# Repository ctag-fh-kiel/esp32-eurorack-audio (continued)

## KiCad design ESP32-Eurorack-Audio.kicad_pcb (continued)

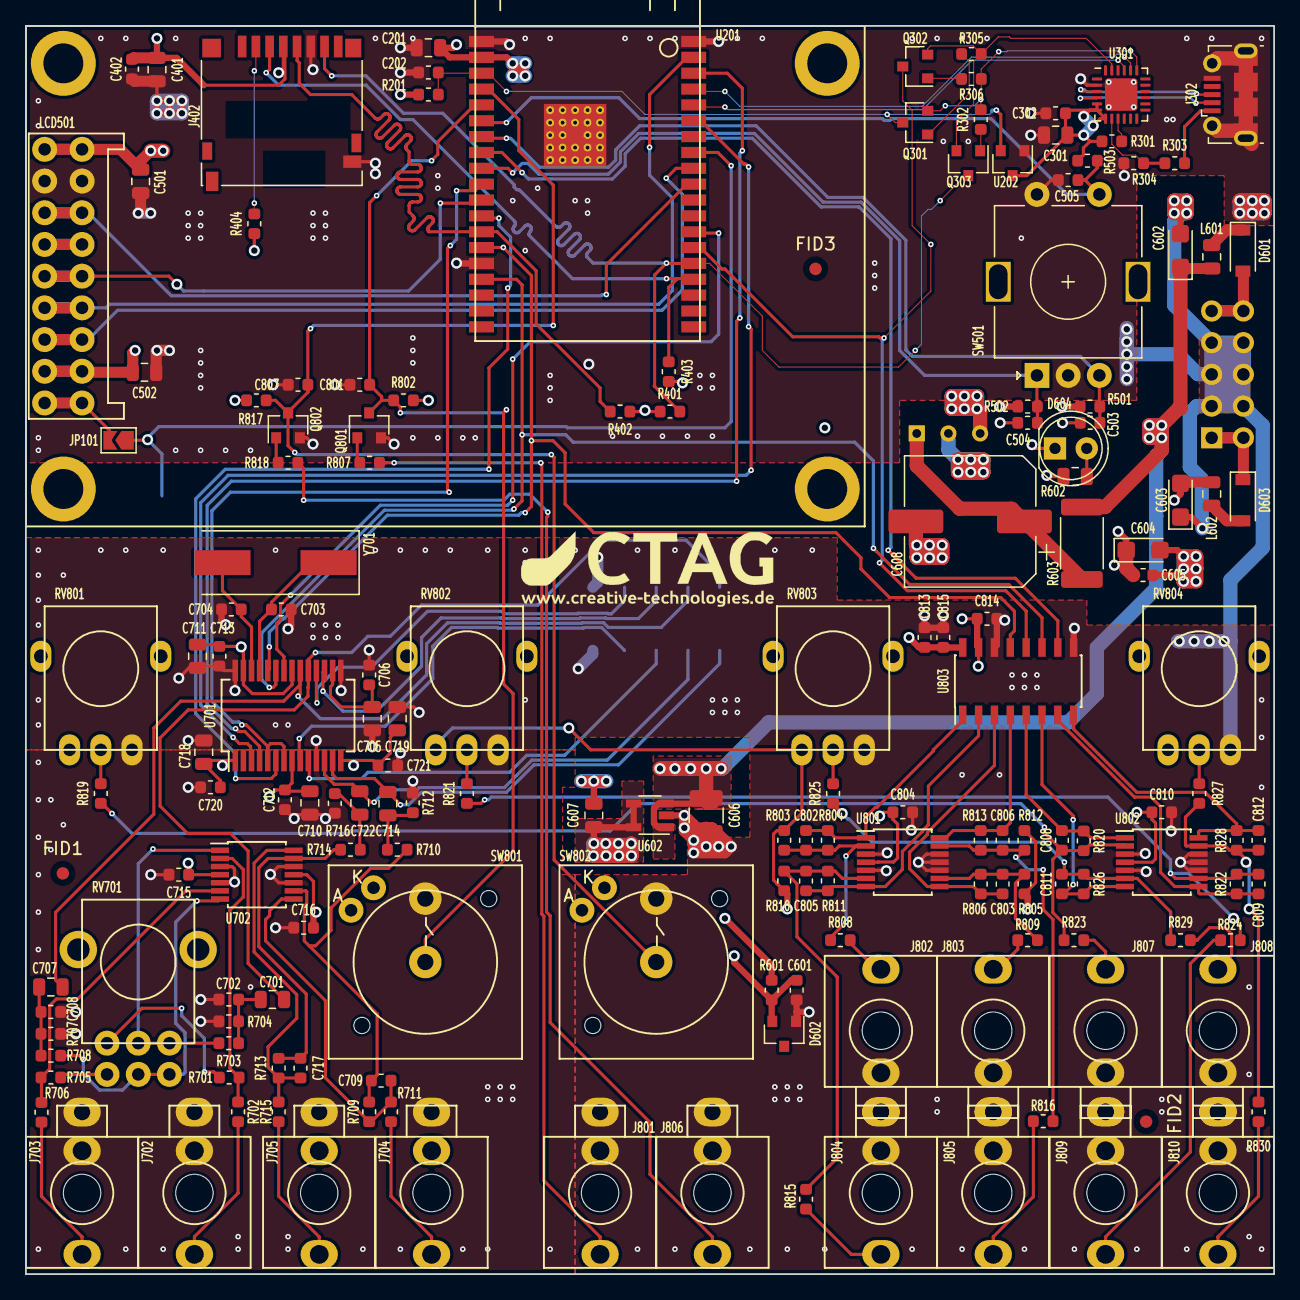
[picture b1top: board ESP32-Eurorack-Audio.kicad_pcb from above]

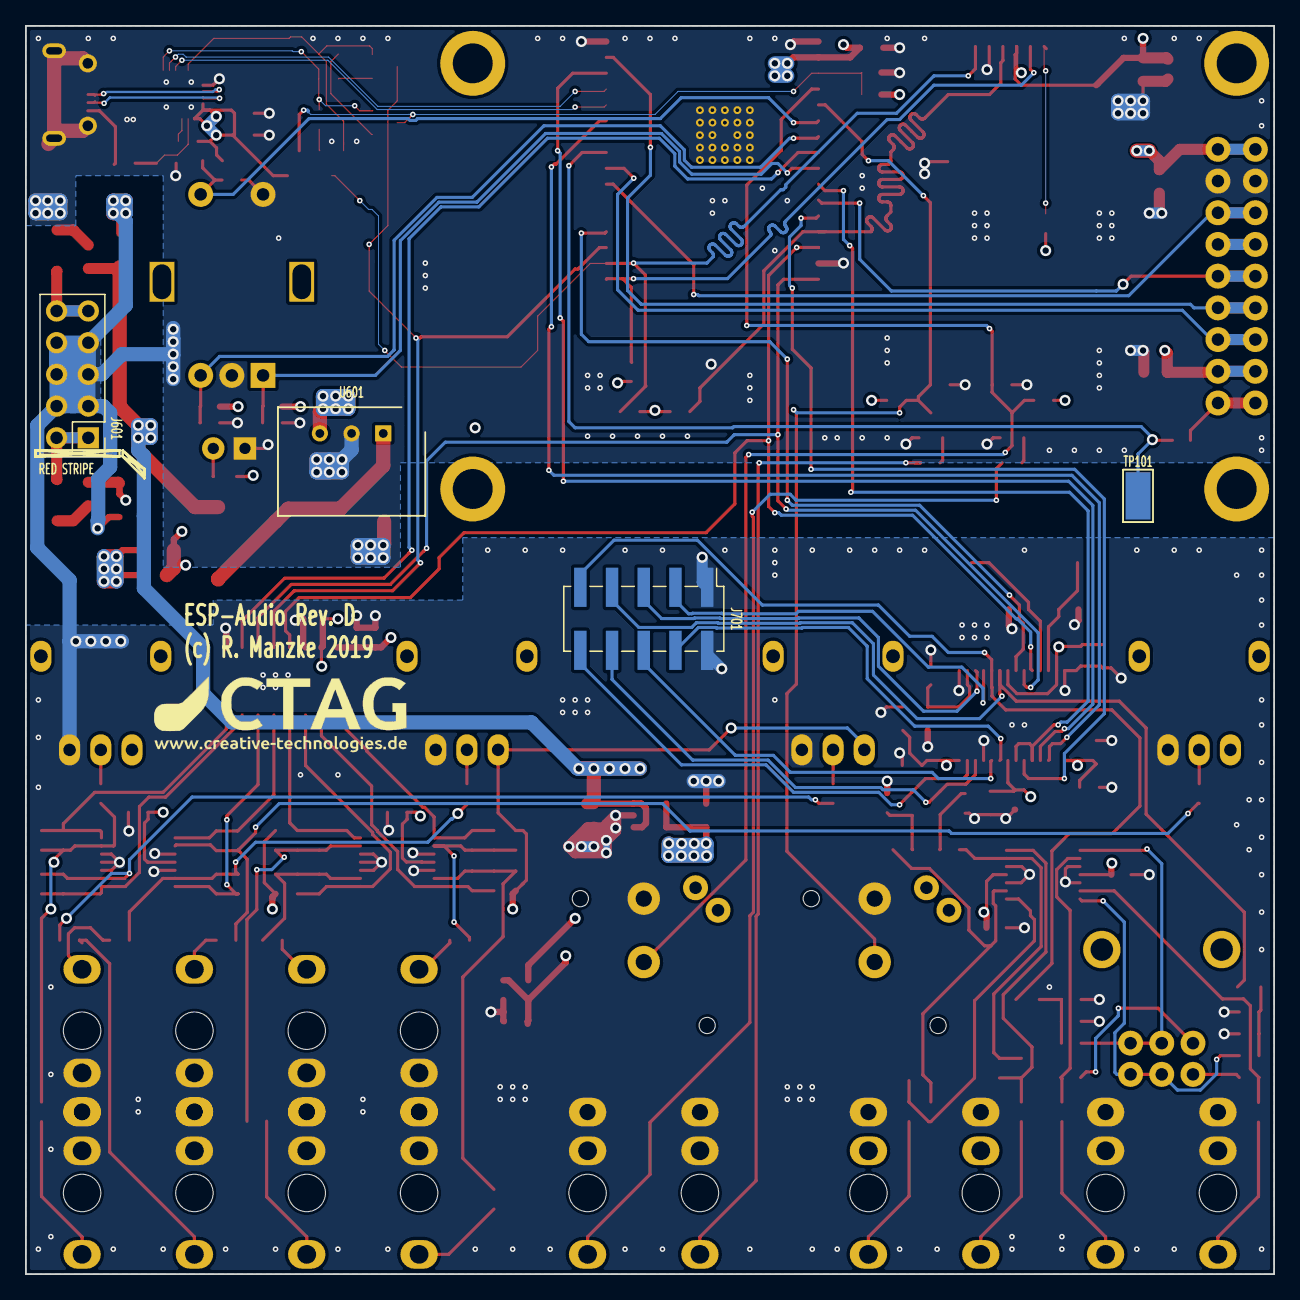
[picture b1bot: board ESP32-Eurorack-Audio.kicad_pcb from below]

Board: 4 copper layers, 100.0 x 100.0 mm, 171 parts (4 on the bottom side), 110 nets.

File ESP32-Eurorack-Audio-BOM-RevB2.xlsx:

Id | Designator | Package | Quantity | Designation | Mouser | Remarks
1 | C813,C302,C402,C601,C605,C706,C712,C715,C716,C720,C721,C801,C804,C807,C810,C713 | C_0603_1608Metric | 16 | 100n | 81-GRM033C71C104KE4J
2 | C815,C814 | C_0603_1608Metric | 2 | 1u | 710-885012206034
3 | U201 | ESP32-WROVER | 1 | ESP32-WROVER | 356-ESP32-WROB(16MB)
 | LCD501 | Connector | 1 |  | MDF7-9S-2.54DSA(55) and MDF7-5S-2.54DSA(55)
4 | LCD501 | TFT_2.2 | 1 | TFT_ILI9341 | https://www.aliexpress.com/item/Smart-Electronics-2-2-Inch-2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 | 2.2" TFT ILI9341 e.g. Aliexpress
5 | C201,C401,C501,C607,C701,C705,C707,C710,C714,C718,C719,C722,C502,C301,C711 | C_0805_2012Metric | 15 | 10u | 81-GRM21BR70J106KA3L
6 | C202 | C_0603_1608Metric | 1 | 3.3u | 963-EMK316B7335KL-T
7 | C204,C802,C803,C805,C806,C808,C809,C811,C812 | C_0603_1608Metric | 9 | 1n | 77-VJ0603Y102KXQCBC
8 | C602,C603,C604 | CP_EIA-3216-12_Kemet-S | 3 | 22u | 581-F951C226KQAAQ2
9 | C702,C708 | C_0603_1608Metric | 2 | 220p | 710-885012206055
10 | C703,C704,C709,C717 | C_0603_1608Metric | 4 | 18p | 80-C0603C180J5G
11 | D301,D601,D603 | D_SOD-123 | 3 | STPS2L40ZFY | 511-STPS2L40ZFY
12 | D302,D401,D402 | SOT-143 | 3 | SP0503BAHT | 576-SP0503BAHTG
13 | D602 | SOT-23 | 1 | LM4040B-10 | 595-LM4040B10IDBZR
14 | D604 | LED_1206_3216Metric_Castellated | 1 | APTD3216SURCK | 604-APTD-3216SURCK
15 | J302 | USB_Micro-B_Molex-105017-0001 | 1 | USB_B_Micro | 105017-0001
16 | J402 | microSD_HC_Hirose_DM3D-SF | 1 | Micro_SD_Card | 798-DM3D-SF
17 | J601 | PinHeader_2x05_P2.54mm_Vertical | 1 | PWR |  | Standard pin header
28 | JP601 | PinHeader_1x03_P2.54mm_Vertical | 1 | VSEL |  | Standard pin header
29 | L301,L601,L602 | C_0805_2012Metric | 3 | 600 | 623-2508056017Y2
30 | Q301,Q302,Q303,Q801,Q802 | SOT-23 | 5 | SS8050-G | 750-SS8050-G
34 | SW201 | SW_SPST_PTS810 | 1 | EN | 611-PTS810SJK250SMTR | Only for test config, not required in production
35 | SW203 | SW_SPST_PTS810 | 1 | FLASH | 611-PTS810SJK250SMTR | Only for test config, not required in production
36 | SW501 | RotaryEncoder_Alps_EC11E-Switch_Vertical_H20mm | 1 | SEL | https://www.aliexpress.com/item/10pcs-Rotary-encoder-code-sw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 | eg Aliexpress
37 | SW801 | SW_6425 | 2 | TRG0 | 979-826.000.071
38 | SW802 | SW_6425 | 2 | TRG1 | 979-6425.0101
39 | U301 | QFN-24-1EP_4x4mm_P0.5mm_EP2.6x2.6mm | 1 | CP2102N-A01-GQFN24 | 634-CP2102NA01GQFN24
40 | U601 | TO-252-2 | 1 | LM1117-3.3 | 926-LM1117DT-3.3NOPB
41 | U602 | TSOT-23-5 | 1 | ADP7118 | 584-ADP7118AUJZ3.3R7
42 | U701 | SSOP-28_5.3x10.2mm_P0.65mm | 1 | WM8731 | 238-WM8731SEDS/V
43 | U702 | TSSOP-14_4.4x5mm_P0.65mm | 1 | TL074 | 595-TL074CPWR
44 | U801,U802 | TSSOP-14_4.4x5mm_P0.65mm | 2 | MCP6004 | 579-MCP6004-I/ST
45 | U803 | SOIC-16_3.9x9.9mm_P1.27mm | 1 | MCP3208 | 579-MCP3208T-CI/SL
46 | Y701 | Crystal_SMD_HC49-SD | 1 | 11.289600MHz | 815-ABLS211.2896B4YT
47 | R201,R301,R302,R305,R306,R401,R402,R403,R404,R501,R502,R503,R801,R802,R814,R817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 | R_0603_1608Metric | 17 | 10k | 652-CR0603FX-1002ELF
48 | R303 | R_0603_1608Metric | 1 | 22.1k | 652-CR0603FX-2212ELF
49 | R304 | R_0603_1608Metric | 1 | 47.5k | 603-RC0603FR-0747K5L
50 | R807,R808,R809,R815,R816,R818,R823,R824,R829,R830 | R_0603_1608Metric | 13 | 100k | 603-RC0603FR-07100KL
51 | R601 | R_0603_1608Metric | 1 | 220
52 | R602 | R_0805_2012Metric | 1 | 68 | 603-AC0603FR-0768RL
53 | R701,R705 | R_0603_1608Metric | 2 | 3k3 | 652-CR0603-FX3301ELF
54 | R702,R706 | R_0603_1608Metric | 2 | 22k | 652-CR0603FX-2202ELF
55 | R703,R704,R707,R708,R710,R714 | R_0603_1608Metric | 6 | 5k6 | 652-CR0603FX-5601ELF
56 | R709,R712,R713,R716 | R_0603_1608Metric | 4 | 39k | 652-CR0603FX-3902ELF
57 | R711,R715,R202,R204 | R_0603_1608Metric | 4 | 1k | 652-CR0603FX-1001ELF
58 | R803,R810 | R_0603_1608Metric | 2 | 180k | 652-CR0603FX-1803ELF
59 | R804,R811 | R_0603_1608Metric | 2 | 47k | 652-CR0603FX-4702ELF
60 | R805,R812,R819,R821,R825,R827 | R_0603_1608Metric | 6 | 200k | 652-CR0603FX-2003ELF
61 | R806,R813 | R_0603_1608Metric | 2 | 33k | 652-CR0603FX-3302ELF
62 | R820,R822,R826,R828 | R_0603_1608Metric | 4 | 66.5k | 652-CR0603-FX6652ELF
63 | J701 | PinHeader_2x05_P2.54mm_Vertical_SMD | 1 | AUEXT |  | Standard SMD pin header
64 | FID1,FID2,FID3 | Fiducial_1mm_Dia_2.54mm_Outer_CopperTop | 3 | ~ |  | Fiducials for pick and place
65 | C606 | C_1210_3225Metric | 1 | 10u | 963-EMK325B7106MN-T
66 | JP101,JP201,JP202 | SolderJumper-2_P1.3mm_Open_TrianglePad1.0x1.5mm | 3 | Jumper |  | Test configs
67 | Q201,Q202 | SOT-23 | 2 | BSS138 | 771-BSS138P215 | Only for test config, not required in production
68 | TP101 | TestPoint_Keystone_5019_Minature | 1 | TP_IO19 | 534-5019 | For testing purposes, only if needed
69 | TP301 | TestPoint_Keystone_5019_Minature | 1 | TP_EN | 534-5019 | For testing purposes, only if needed
70 | TP302 | TestPoint_Keystone_5019_Minature | 1 | TP_IO0 | 534-5019 | For testing purposes, only if needed
71 | TP303 | TestPoint_Keystone_5019_Minature | 1 | TP_IO2 | 534-5019 | For testing purposes, only if needed
72 | TP602 | TestPoint_Keystone_5019_Minature | 1 | TestPoint | 534-5019 | For testing purposes, only if needed
73 | TP801 | TestPoint_Keystone_5019_Minature | 1 | TA | 534-5019 | For testing purposes, only if needed
74 | TP802 | TestPoint_Keystone_5019_Minature | 1 | TB | 534-5019 | For testing purposes, only if needed
75 | TP803 | TestPoint_Keystone_5019_Minature | 1 | TC | 534-5019 | For testing purposes, only if needed
76 | TP304 | TestPoint_Keystone_5019_Minature | 1 | TP_RXD | 534-5019 | For testing purposes, only if needed
77 | TP305 | TestPoint_Keystone_5019_Minature | 1 | TP_TXD | 534-5019 | For testing purposes, only if needed
78 | TP306 | TestPoint_Keystone_5019_Minature | 1 | TP_DTR | 534-5019 | For testing purposes, only if needed
79 | TP307 | TestPoint_Keystone_5019_Minature | 1 | TP_RTS | 534-5019 | For testing purposes, only if needed

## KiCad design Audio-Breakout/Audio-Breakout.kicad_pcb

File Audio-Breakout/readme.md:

# Stereo line IO + headphones breakout board for ESP32 Eurorack Audio Synthesis Module

Licensed under CC BY-NC-SA 4.0
https://creativecommons.org/licenses/by-nc-sa/4.0/
(C) Robert Manzke 2019

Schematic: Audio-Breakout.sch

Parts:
C1, C4, C5, C7, C9: 1u; C_0603_1608Metric
C2, C3: 220u; CP_Elec_10x10.5
C6, C8, C10: 220p; C_0603_1608Metric
FID1, FID2, FID3: Fiducial_1mm_Dia_2.54mm_Outer_CopperTop
J1: LINEOUT; PJ-301CM
J2: HPOUT; PJ-301CM
J3: AUEXT; PinHeader_2x05_P2.54mm_Vertical
J4: LINEIN; PJ-301CM
J5: MICIN; THONKICONN
R1, R4: 100; R_0603_1608Metric
R2, R3, R5, R6, R11: 47k; R_0603_1608Metric
R7, R9, R12, R13: 5k6; R_0603_1608Metric
R8: 680; R_0603_1608Metric
R10: RMIC; R_0603_1608Metric

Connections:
/LHPOUT: C2.1, J3.4
/LIN: C5.1, J3.7
/LOUT: C1.2, J3.8
/MICBIAS: J3.5, R8.1
/MICIN: J3.3, R10.1
/RHPOUT: C3.1, J3.6
/RIN: C9.1, J3.9
/ROUT: C4.2, J3.10
GND: C6.1, C8.1, C10.1, J1.S, J2.S, J3.1, J3.2, J4.S, J5.2, J5.3, R2.2, R3.2, R5.2, R6.2, R9.2, R11.2, R13.2
unnamed: C1.1, R1.2, R2.1
unnamed: C2.2, J2.T, R3.1
unnamed: C3.2, J2.R, R5.1
unnamed: C4.1, R4.2, R6.1
unnamed: C5.2, C6.2, R7.1, R9.1
unnamed: C7.1, R10.2
unnamed: C7.2, C8.2, J5.1, R8.2, R11.1
unnamed: C9.2, C10.2, R12.1, R13.1
unnamed: J1.R, R4.1
unnamed: J1.T, R1.1
unnamed: J4.R, R12.2
unnamed: J4.T, R7.2

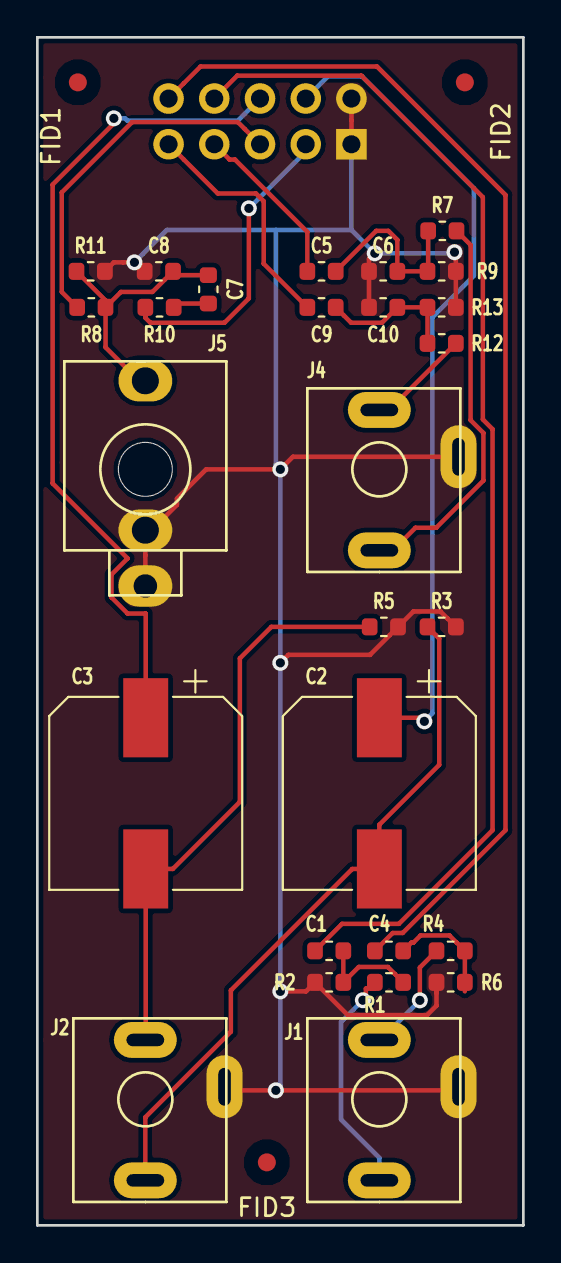
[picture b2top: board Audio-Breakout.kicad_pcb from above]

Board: 2 copper layers, 27.0 x 66.0 mm, 31 parts (1 on the bottom side), 21 nets.

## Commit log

2019-03-27 initial
2019-03-27 libs added
2019-04-27 current
2019-04-27 updated files
2019-05-03 added frontplate design file
2019-05-03 images + readme
2019-05-13 cleaned up schematic
2019-05-13 PCB and BOM updated, cleanups
2019-05-14 frontplate design rework
2019-05-15 more frontplate design
2019-05-15 cleanups and gerbers
2019-05-17 sending for production
2019-05-25 updated bom
2019-06-04 BOM errors fixed
2019-06-13 added pcb fiducials, updated date
2019-06-14 gerber files updated, silkscreen fixed
